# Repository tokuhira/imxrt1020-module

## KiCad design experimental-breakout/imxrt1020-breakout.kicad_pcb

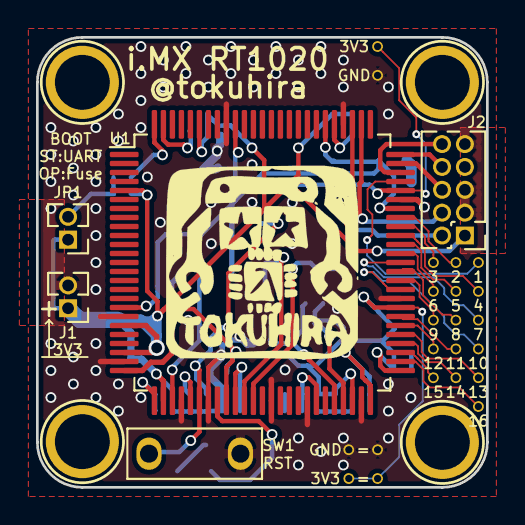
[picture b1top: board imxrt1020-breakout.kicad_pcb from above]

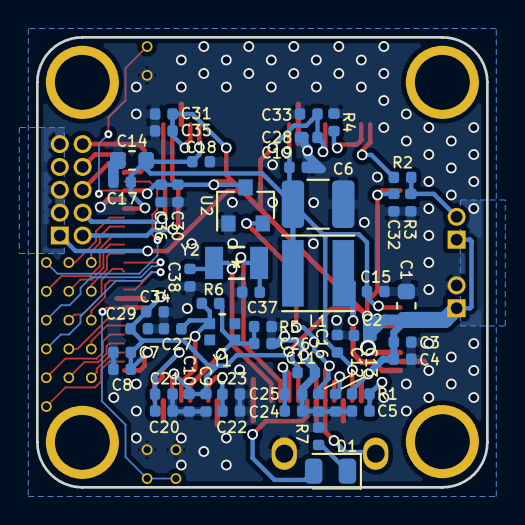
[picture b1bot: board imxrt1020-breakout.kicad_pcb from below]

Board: 2 copper layers, 25.0 x 25.0 mm, 81 parts (50 on the bottom side), 40 nets.

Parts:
1, 2, 3, 3V3, 3V3#2, 4, 5, 6, 7, 8, 9, 10, 11, 12, 13, 14, 15, 16: TestPoint; VIA_Hole
=: TestPoint; VIA_Hole
=#2: TestPoint; VIA_Hole
C1, C14: 22u; C_0603_1608Metric
C2, C4, C5, C8, C10, C11, C13, C15, C16, C17, C18, C19, C21, C23, C25, C32, C33, C34, C35, C36: 0.22u; C_0402_1005Metric
C3, C9, C20, C22, C24, C28, C29, C30, C31: 4.7u; C_0402_1005Metric
C6: 33u; C_1210_3225Metric
C7, C12: 1u; C_0402_1005Metric
C26, C27: 4.7p; C_0402_1005Metric
C37, C38: 7p; C_0402_1005Metric
D1: LED_ALT; LED_0805_2012Metric
GND: TestPoint; VIA_Hole
GND#2: TestPoint; VIA_Hole
J1: Conn_Coaxial_Power; PinHeader_1x02_P1.27mm_Vertical
J2: Conn_02x05_Odd_Even; PinHeader_2x05_P1.27mm_Vertical
JP1: ROMBOOT; PinHeader_1x02_P1.27mm_Vertical
L1: 4.7u; L_Taiyo-Yuden_MD-4040
P5, P6, P7, P8: CONN_01X01; Arduino_1pin
R1, R4: 30k; R_0402_1005Metric
R2: 10k; R_0402_1005Metric
R3, R7: 1k; R_0402_1005Metric
R5: 2.2M; R_0402_1005Metric
R6: 1M; R_0402_1005Metric
SW1: SW_Push_45deg; SW_Tactile_2P_50mil
U1: MIMXRT1021-LQFP100; LQFP-100_14x14mm_P0.5mm
U2: TPS3839DBZ; SOT-23
Y1: XRCGB24M000F2P00R0
Y2: Q13FC1350000200

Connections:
+3V3: 3V3.1, 3V3#2.1, =.1, C1.1, C2.1, C3.1, C4.1, C7.1, C8.1, C9.1, C10.1, C11.1, C28.1, C29.1, C30.1, C31.1, C32.1, C33.1, C34.1, C35.1, C36.1, J1.1, J2.1, JP1.1, R1.1, U1.5, U1.20, U1.23, U1.27, U1.34, U1.48, U1.51, U1.58, U1.71, U1.80, U1.95, U2.3
/BOOT_MODE0: R2.2, U1.100
/BOOT_MODE1: R4.2, U1.99
/DCDC_LP: L1.1, U1.25
/DCDC_OUT: C6.1, C14.1, C15.1, C16.1, C17.1, C18.1, C19.1, L1.2, U1.18, U1.28, U1.69, U1.81, U1.91
/DCDC_PSWITCH: C5.1, R1.2, U1.26
/NVCC_PLL: C20.1, C21.1, U1.50
/ONOFF: C13.1, U1.30
/PMIC_ON_REQ: D1.2, U1.33
/POR_B: C12.1, SW1.1, U1.31, U2.2
/VDD_HIGH_CAP: C22.1, C23.1, U1.44
/VDD_SNVS_CAP: C24.1, C25.1, U1.35
GND: =#2.1, C1.2, C2.2, C3.2, C4.2, C5.2, C6.2, C7.2, C8.2, C9.2, C10.2, C11.2, C12.2, C13.2, C14.2, C15.2, C16.2, C17.2, C18.2, C19.2, C20.2, C21.2, C22.2, C23.2, C24.2, C25.2, C26.2, C27.2, C28.2, C29.2, C30.2, C31.2, C32.2, C33.2, C34.2, C35.2, C36.2, C37.2, C38.2, GND.1, GND#2.1, J1.2, J2.3, J2.5, J2.9, R3.2, R4.1, R5.2, R7.1, SW1.2, U1.19, U1.24, U1.29, U1.32, U1.39, U1.43, U1.49, U1.59, U1.70, U1.79, U1.92, U2.1
unnamed: C26.1, R5.1, R6.2, U1.46, Y1.1
unnamed: C27.1, R6.1, U1.47, Y1.3
unnamed: C37.1, U1.36, Y2.1
unnamed: C38.1, U1.37, Y2.2
unnamed: D1.1, R7.2
unnamed: J2.2, U1.78
unnamed: J2.4, U1.77
unnamed: J2.6, U1.74
unnamed: J2.8, U1.75
unnamed: J2.10, U1.73
unnamed: JP1.2, R2.1, R3.1
unnamed: 1.1, U1.72
unnamed: 2.1, U1.68
unnamed: 3.1, U1.67
unnamed: 4.1, U1.66
unnamed: 5.1, U1.65
unnamed: 6.1, U1.64
unnamed: 7.1, U1.63
unnamed: 8.1, U1.62
unnamed: 9.1, U1.61
unnamed: 10.1, U1.60
unnamed: 11.1, U1.57
unnamed: 12.1, U1.56
unnamed: 13.1, U1.55
unnamed: 14.1, U1.54
unnamed: 15.1, U1.53
unnamed: 16.1, U1.52

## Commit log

2020-04-09 Create experimental-breakout board
    Extracted basic circuit from imxrt1020-module into 25x25 with LQFP100.
2020-04-10 Update imxrt1020-breakout.sch
    Added LCSC parts no.
    Changed C6: 33u => 47u
    Changed L1: Taiyo-Yuden => 3rd party
2020-04-10 Generate the BOM and Centroid file
    In order to JLCPCB SMT Assenbry service.
2020-04-11 Update imxrt1020-breakout
    Fixed top side silk.
    Fixed parts mounting property.
2020-04-15 Update imxrt1020-breakout
    Added paste files.
2020-04-15 Update imxrt1020-breakout.kicad_pcb
    Added paste files.

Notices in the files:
parts and their libraries:
Copyright 2016 Accelerated Designs. All rights reserved.
